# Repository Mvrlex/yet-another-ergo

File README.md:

# yet-another-ergo

The climax of my split custom keyboard journey. My own custom ergo unibody keyboard.
Inspired by the [Cantor](https://github.com/diepala/cantor) and
[Kaly](https://github.com/Dwctor/Kaly).

Thanks to [FlatFootFox](https://flatfootfox.com/). Without your blog series this would not
have been possible.

### The why

I created this because I wasn't really satisfied with the available offerings, the 
closest thing to what I wanted was a [Cantor](https://github.com/diepala/cantor), which I
have built, but I wanted to try an even more aggressive stagger, which spurred the
creation of yet-another-ergo keyboard.

### The creation

Working on this was really fun. From designing the board, to creating the PCB and 
assembling it. Funnily enough the programming part, which I should have been most 
familiar with, was the most frustrating part. I found a lot of conflicting information 
online about how to set QMK up and how to use it. It seemed like there is a dozen ways 
to do the same thing, and using one breaks the other. The minimalist examples didn't 
really help either. I think I get how QMK works now, but in the end I gave up on 
creating my keymap in code, and simply used Vial (because Via can't do Tap-Dances?) to 
set it up. That's why the keymap.json is so barren :D

### The journey

I like mechanical keyboards, and I like modding and customizing them. After finding my
favorite TKL-ish keyboard, the Akko 5075, I started noticing that I made a lot of mistakes
when typing. So I set out to learn touch typing. Which was fine, but I soon learned that
my hands were not really the problem, but the keyboard layout. The german QWERTZ layout
absolutely sucks for programming, pretty much all the symbols are hard to reach and require
a modifier key.

I then found [Ben Vallack](https://www.youtube.com/@BenVallack)s YouTube channel, and
fell down the rabbit hole of split keyboards. They looked sick, and promised all these
benefits, but they also were incredibly expensive So I went all in and built myself a 
[Cheapino](https://github.com/tompi/cheapino).  
I loved it. Ortholinear keys for sensible finger movements, split design for better
ergonomics, and a thumb cluster to use the thumbs a bit more. However, after trying to use
it for programming I realized that I'm missing a few keys, and the numbers were hard to
type.  
So next up was the [Silakka54](https://github.com/Squalius-cephalus/silakka54). This is
where I stayed a bit and learned what I liked and what I didn't like. I definitely wanted
a more aggressive stagger, a more compact layout for less finger travel, and a thumb 
cluster that did not break my wrists when using it (seriously, wtf). I also would like 
for the keyboard to look nice.

This is when I started looking for the perfect keyboard for me, and honestly, the closest
thing I found was [Kaly](https://github.com/Dwctor/Kaly) a derivative of the Cantor, but
I didn't really like the design, I didn't want another split, and I wanted a smaller thumb
cluster. So at that point why not just design my own?

### Did I succeed?

No.

After starting the journey of creating my own keyboard I realized that I would not be 
able to achieve my initial goal of making less mistakes with such a keyboard. Maybe 
after years of use and a lot of fine-tuning.

#### What I don't like

- layer switching is a pain when typing fast
- typing numbers is hard, even with practice
- home-row mods (or for me bottom-row mods) are too inconsistent
- long typing sessions are actually uncomfortable, because of the forced use of my 
  pinky and ring finger
- I can't type some keys when my hand is on the mouse, which breaks my flow

##### What I like

- it's fun
- it looks cool
- ortholinear keys just make sense
- higher typing speed, with greater potential for improvement
- tap-dances for keys like ä, ö, ü, and ß are great
- the position of backspace, enter and escape on the outermost keys is great
- osm shift as a thumb key is great
- minimalist design and more space on the desk

### What's next?

I think I will stick with what I have for now. I will try to get used to it. If I 
can't, I will either go back to my lovely TKL or I will build another custom keyboard 
similar to the X-Bows Ergo, which I think is a pretty good compromise.

### Thank you

Thank you for reading this far. If you liked my little ramble, please consider
starring the project. I do need me some of that internet clout ;)

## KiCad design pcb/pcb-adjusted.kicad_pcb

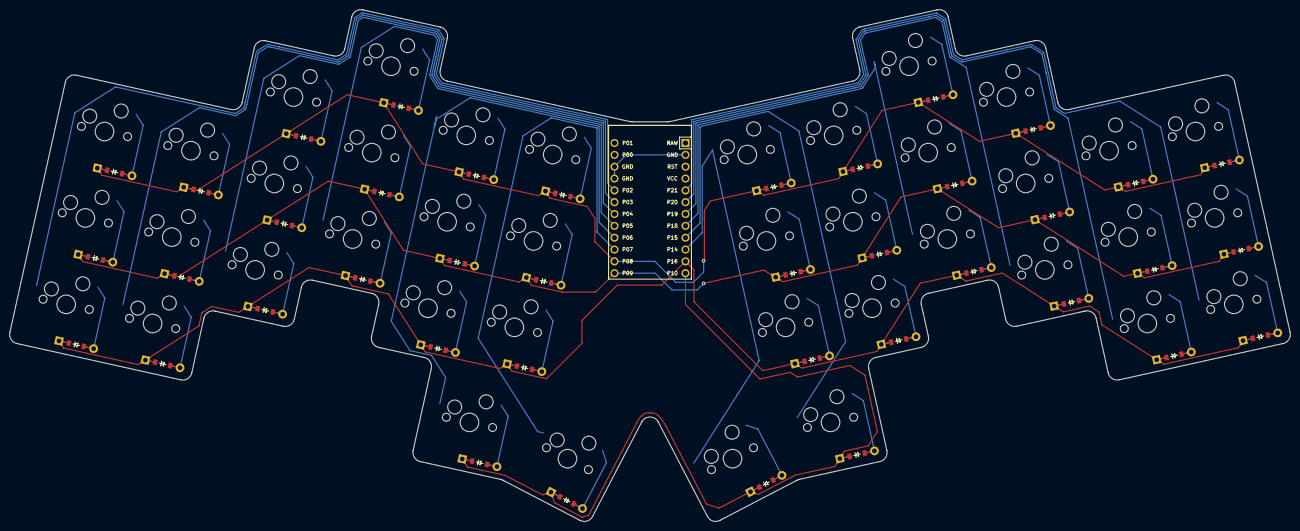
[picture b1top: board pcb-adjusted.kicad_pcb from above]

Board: 2 copper layers, 274.9 x 109.9 mm, 81 parts (0 on the bottom side), 57 nets.

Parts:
D1, D2, D3, D4, D5, D6, D7, D8, D9, D10, D11, D12, D13, D14, D15, D16, D17, D18, D19, D20, D21, D22, D23, D24, D25, D26, D27, D28, D29, D30, D31, D32, D33, D34, D35, D36, D37, D38, D39, D40: ComboDiode
MCU1: ProMicro
S1, S2, S3, S4, S5, S6, S7, S8, S9, S10, S11, S12, S13, S14, S15, S16, S17, S18, S19, S20, S21, S22, S23, S24, S25, S26, S27, S28, S29, S30, S31, S32, S33, S34, S35, S36, S37, S38, S39, S40: MX

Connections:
GND: MCU1.2, MCU1.15, MCU1.16
P2: MCU1.17, S1.1, S2.1, S3.1
P3: MCU1.18, S4.1, S5.1, S6.1
P4: MCU1.19, S7.1, S8.1, S9.1
P5: MCU1.20, S10.1, S11.1, S12.1
P6: MCU1.21, S13.1, S14.1, S15.1, S19.1
P7: MCU1.22, S16.1, S17.1, S18.1, S20.1
P8: D3.1, D6.1, D9.1, D12.1, D15.1, D18.1, D23.1, D26.1, D29.1, D32.1, D35.1, D38.1, MCU1.23
P9: D2.1, D5.1, D8.1, D11.1, D14.1, D17.1, D22.1, D25.1, D28.1, D31.1, D34.1, D37.1, MCU1.24
P10: D19.1, D20.1, D39.1, D40.1, MCU1.12
P14: MCU1.10, S36.1, S37.1, S38.1, S40.1
P15: MCU1.9, S33.1, S34.1, S35.1, S39.1
P16: D1.1, D4.1, D7.1, D10.1, D13.1, D16.1, D21.1, D24.1, D27.1, D30.1, D33.1, D36.1, MCU1.11
P18: MCU1.8, S30.1, S31.1, S32.1
P19: MCU1.7, S27.1, S28.1, S29.1
P20: MCU1.6, S24.1, S25.1, S26.1
P21: MCU1.5, S21.1, S22.1, S23.1
home_thumb: D20.2, S20.2
index_bottom: D13.2, S13.2
index_home: D14.2, S14.2
index_top: D15.2, S15.2
inner_bottom: D16.2, S16.2
inner_home: D17.2, S17.2
inner_top: D18.2, S18.2
middle_bottom: D10.2, S10.2
middle_home: D11.2, S11.2
middle_top: D12.2, S12.2
mirror_home_thumb: D40.2, S40.2
mirror_index_bottom: D33.2, S33.2
mirror_index_home: D34.2, S34.2
mirror_index_top: D35.2, S35.2
mirror_inner_bottom: D36.2, S36.2
mirror_inner_home: D37.2, S37.2
mirror_inner_top: D38.2, S38.2
mirror_middle_bottom: D30.2, S30.2
mirror_middle_home: D31.2, S31.2
mirror_middle_top: D32.2, S32.2
mirror_near_thumb: D39.2, S39.2
mirror_outer_bottom: D21.2, S21.2
mirror_outer_home: D22.2, S22.2
mirror_outer_top: D23.2, S23.2
mirror_pinky_bottom: D24.2, S24.2
mirror_pinky_home: D25.2, S25.2
mirror_pinky_top: D26.2, S26.2
mirror_ring_bottom: D27.2, S27.2
mirror_ring_home: D28.2, S28.2
mirror_ring_top: D29.2, S29.2
near_thumb: D19.2, S19.2
outer_bottom: D1.2, S1.2
outer_home: D2.2, S2.2
outer_top: D3.2, S3.2
pinky_bottom: D4.2, S4.2
pinky_home: D5.2, S5.2
pinky_top: D6.2, S6.2
ring_bottom: D7.2, S7.2
ring_home: D8.2, S8.2
ring_top: D9.2, S9.2

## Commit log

2025-03-02 feat: add first pcb and switchplate design
2025-04-27 feat: add firmware
    Took 2 hours 41 minutes
2025-04-27 docs: write something about the board
    Took 2 minutes
